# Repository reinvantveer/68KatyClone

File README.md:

# 68KatyClone
An open-hardware design for an 8-bit Motorola 68008 system.
Please feel free to re-use any of the parts enclosed in this repository, or see the [license](./LICENSE) for the hardware if in doubt.
However, the [monitor](Software/ROM/monitor.asm) and [Linux image](https://www.bigmessowires.com/68katy-files/uClinux-20040218.tar.gz) are both GNU GPL licensed, so these need care. Since I can't include the modified Linux image files in this repository itself (the file is too large to be included), I'll suffice by pointing you to [with a link](https://www.bigmessowires.com/68katy-files/uClinux-20040218.tar.gz). This was adapted from the [uCLinux original](https://web.archive.org/web/20181014184953/http://www.uclinux.org/pub/uClinux/dist/uClinux-dist-20040218.tar.gz). Ironically, the compiled binary image is small enough to fit into the 512k ROM, of course. 

**NOTE** This is a work in progress, by a guy with no prior experience in CPU board prototyping. Although I'm enjoying myself thoroughly and things are progressing well, this project comes without guarantees. 
* Update 17-03-202: I got my first address and data bus readouts today, using an Arduino Mega. It's not making much sense to me yet, but it soon will. It's clear that the processor is executing instructions!
* Update 15-03-2020: There is a working ['single-stepping' and power-up/reset schematic](KiCad/single-stepping.sch) that will serve as the basis for the rest of the project. The rest may or may not work, I'm not done debugging yet. 
* Update 22-03-2020: Made a few huge steps forward in having a working board, but I can't get a decent serial readout yet.  

# Credits
* This repository is my attempt to build a re-vamped edition of Steve "Big Mess-O-Wires" Chamberlin's [68Katy](https://www.bigmessowires.com/68-katy/), for which I owe him many thanks. It's my first go at breadboard prototyping, but since I'm learning so much I thought I'd contribute by publishing my findings. It has been quite the ride thus far. 
* Also, I'd like to point to Ben Eater's [6502 project](https://eater.net/6502), which has been quite inspirational. 
* I got myself a scope based on YouTubers [Adrians Digital Basement](https://www.youtube.com/channel/UCE5dIscvDxrb7CD5uiJJOiw) and [EEVblog](https://www.youtube.com/channel/UC2DjFE7Xf11URZqWBigcVOQ). 
* The [vid by John Tsiombikas](https://www.youtube.com/watch?v=rYkr1mFQ_50) helped me out hugely in putting together the single-stepping part of the board.  
* The power-up/reset circuit was based on a design [published by Jeff Tranter](https://github.com/jefftranter/68000/blob/master/TS2/v2.1/page1.sch)

I'm using the [68Katy](https://www.bigmessowires.com/68-katy/) design because it's pretty well documented, as Motorola 68K projects go. There's a lot of people experimenting, I even believe there's some kind of revival going of people baking 8-bit systems just for fun. The fact that a lot of the components can be ordered over the mail very cheaply most certainly adds to the fun - parts are available in abundance and even the shipping is often very cheap if you're willing to wait a couple of weeks. My guess is that these kinds of projects are being undertaken by late-30's to mid-50's guys tinkering away in sheds and attics. I happen to be just one of them. 

The reason I wanted to do a 68K project, is because I used to be, and still am, the proud owner of a Texas Instruments TI-92 that I bought in high school. At the time, I thought of it as a marvel of technology. I dabbled unsuccessfully in some C++ coding (I found it too hard), but the TI-92 allowed on-board BASIC programming an fancy graph plotting. So there my journey began. Now, over 20 years later, I'm a professional software developer and I believe I'm now better equipped for taking on the challenge of building an 8-bit system from bare components.

# Schematics
The [KiCad](KiCad) folder contains a work-in-progress translation of the schematics from Steve Chamberlin, updating it to a more modern version. I'm working on a board but at the moment it's not working. So use at your own peril.

# Memory Map

BREADBOARD 68 KATY
00000 - 77FFF : ROM
78000 - 79FFF : serial in        
7A000 - 7BFFF : serial out       
7C000 - 7DFFF : serial status    
7E000 - 7FFFF : LED register     
80000 - FFFFF : RAM              

# Software
## ROM image
The [ROM](Software/ROM) folder contains the ROM image: the monitor program and the Linux image. Send it to the ROM using a ROM programmer, I used a [TL866II plus](https://www.aliexpress.com/item/32963724045.html)

## GAL image
The [GAL/68katy](Software/GAL/68katy) folder contains the .jed compiled image. Send it to the GAL using a GAL-compatible ROM programmer, I used a [TL866II plus](https://www.aliexpress.com/item/32963724045.html)
For good measure I also included the [OpalJR compiler](Software/GAL/opaljr21) - as the license seems to allow it; I got it from [here](http://www.brouhaha.com/~eric/retrocomputing/mmi/palasm/opaljr21.zip). There's no reason not to include it here - it's the same program the original 68Katy GAL used to compile so it *should* be OK, although I can never be 100% sure unless I compare the JEDEC compiled file to the original (which I can't). Since it's a 16-bit DOS program, you need something like [DOSBox](https://www.dosbox.com/download.php?main=1) to run it.

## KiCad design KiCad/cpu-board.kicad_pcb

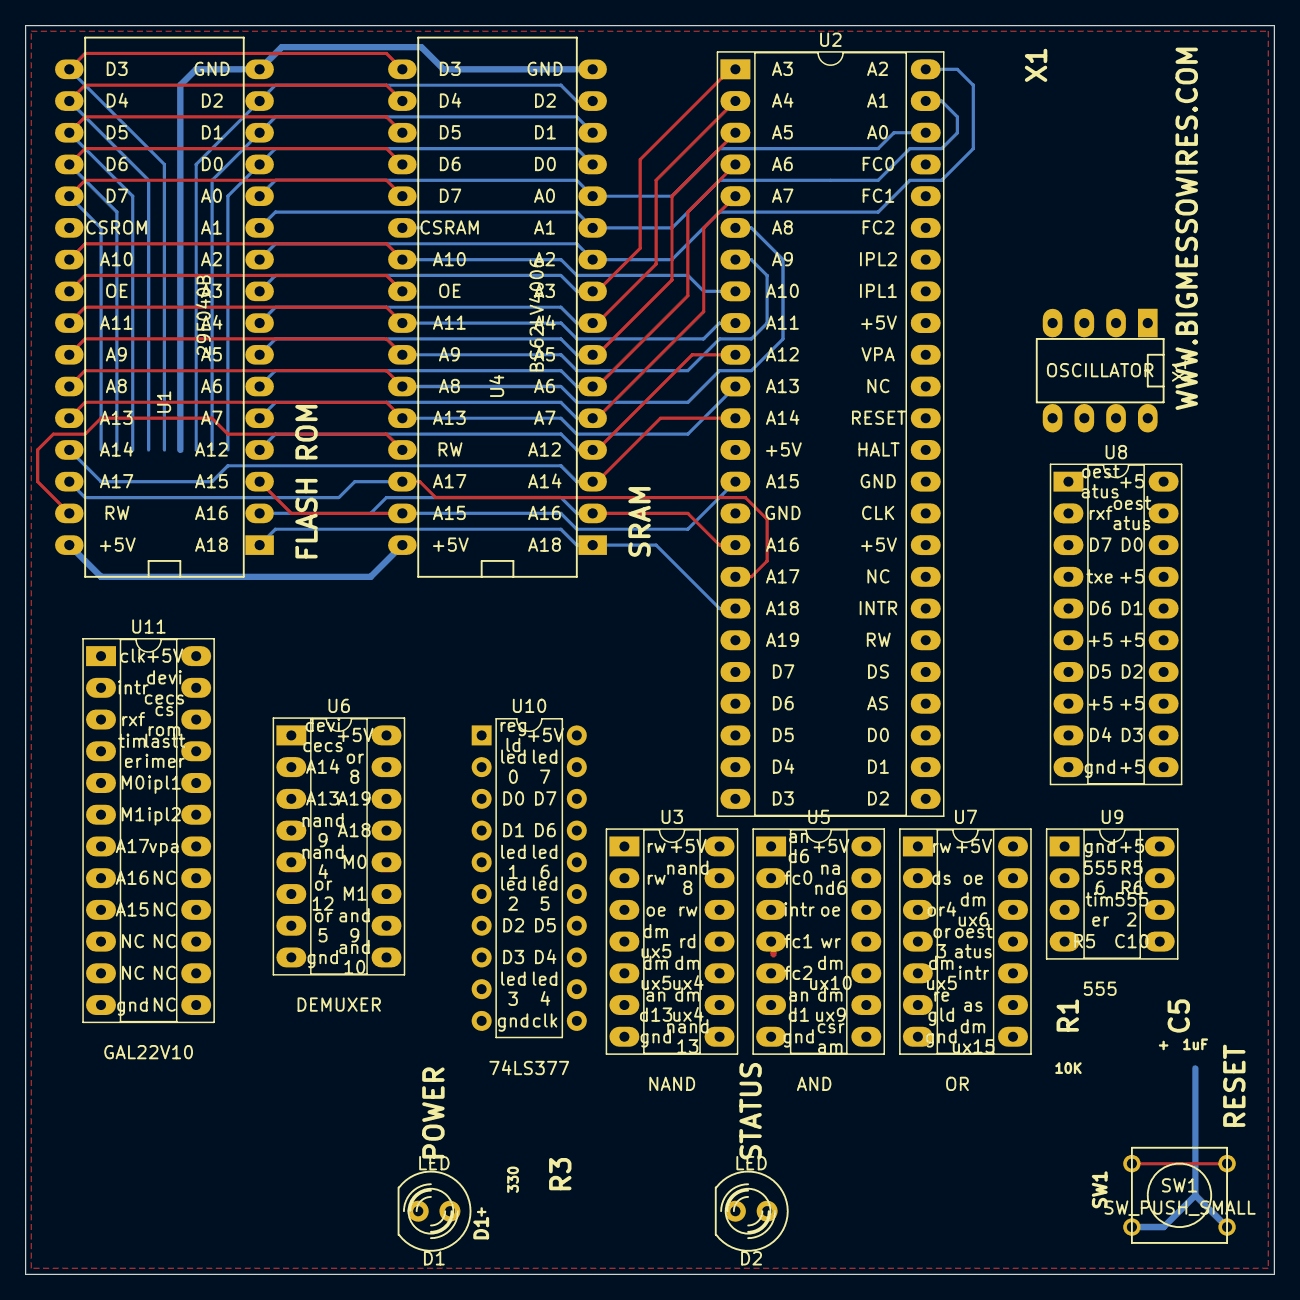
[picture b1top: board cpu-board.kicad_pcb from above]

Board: 2 copper layers, 100.0 x 100.0 mm, 15 parts (0 on the bottom side), 64 nets.

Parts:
D1, D2: LED; LED-5MM
SW1: SW_PUSH_SMALL
U1: 29F040B; DIP-32__600_ELL
U2: 68008D; DIP-48_W15.24mm_Socket_LongPads
U3: 74LS00; DIP-14_W7.62mm_Socket_LongPads
U4: BS62LV4006; DIP-32__600_ELL
U5: 74LS08; DIP-14_W7.62mm_Socket_LongPads
U6: 74LS139; DIP-16_W7.62mm_Socket_LongPads
U7: 74LS32; DIP-14_W7.62mm_Socket_LongPads
U8: 74LS244; DIP-20_W7.62mm_Socket_LongPads
U9: LM555; DIP-8_W7.62mm_Socket_LongPads
U10: 74LS377
U11: GAL22V10
X1: OSCILLATOR; DIP-8__300_ELL

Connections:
+5V: U1.32, U2.13, U2.33, U2.40, U4.32, U6.16, U8.6, U8.8, U8.11, U8.13, U8.15, U8.17, U8.20, U9.8, U10.20, U11.24, X1.8
/A0: U1.12, U2.46, U4.12
/A1: U1.11, U2.47, U4.11
/A2: U1.10, U2.48, U4.10
/A3: U1.9, U2.1, U4.9
/A4: U1.8, U2.2, U4.8
/A5: U1.7, U2.3, U4.7
/A6: U1.6, U2.4, U4.6
/A7: U1.5, U2.5, U4.5
/A8: U1.27, U2.6, U4.27
/A9: U1.26, U2.7, U4.26
/A10: U1.23, U2.8, U4.23
/A11: U1.25, U2.9, U4.25
/A12: U1.4, U2.10, U4.4
/A13: U1.28, U2.11, U4.28, U6.3
/A14: U1.29, U2.12, U4.3, U6.2
/A15: U1.3, U2.14, U4.31, U11.9
/A16: U1.2, U2.16, U4.2, U11.8
/A17: U1.30, U2.17, U4.30, U11.7
/A18: U1.1, U2.18, U4.1, U6.13
/A19: U2.19, U6.14
/AS: U2.28, U7.9
/CLK: U2.34, U10.11, U11.1, X1.5
/CSRAM: U4.22, U5.8
/CSROM: U1.22, U11.22
/D0: U1.13, U2.27, U4.13, U8.18, U10.3
/D1: U1.14, U2.26, U4.14, U8.16, U10.4
/D2: U1.15, U2.25, U4.15, U8.14, U10.7
/D3: U1.17, U2.24, U4.17, U8.12, U10.8
/D4: U1.18, U2.23, U4.18, U8.9, U10.13
/D5: U1.19, U2.22, U4.19, U8.7, U10.14
/D6: U1.20, U2.21, U4.20, U8.5, U10.17
/D7: U1.21, U2.20, U4.21, U8.3, U10.18
/DEVICECS: U6.1, U11.23
/DS: U2.29, U7.2
/FC0: U2.45, U5.2
/FC1: U2.44, U5.4
/FC2: U2.43, U5.5
/INTR: U2.31, U5.3, U7.10, U11.2
/IPL1: U2.41, U11.20
/IPL2: U2.42, U11.19
/M0: U6.12, U11.5
/M1: U6.11, U11.6
/OE: U1.24, U3.3, U4.24, U5.12, U7.13
/OESTATUS: U7.11, U8.1, U8.19
/REGLD: U7.6, U10.1
/RESET: SW1.1, U2.37
/RW: U1.31, U2.30, U3.1, U3.2, U3.12, U4.29, U7.1
/RXF: U8.2, U11.3
/TIMER: U9.3, U11.4
/VPA: U2.39, U11.18
GND: D1.2, SW1.2, U1.16, U2.15, U2.35, U4.16, U6.8, U8.10, U9.1, U10.10, U11.12, X1.4
unnamed: U9.2, U9.6
unnamed: U3.4, U3.5, U6.5
unnamed: U3.6, U5.13
unnamed: U3.9, U3.10, U6.4
unnamed: U3.8, U3.13
unnamed: U5.1, U5.6
unnamed: U5.9, U6.9
unnamed: U5.10, U6.10
unnamed: U6.6, U7.12
unnamed: U6.7, U7.5
unnamed: U6.15, U7.8
unnamed: U7.3, U7.4

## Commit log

2020-01-26 Rationale
2020-02-01 Include first rough version of KiCad schematics
2020-02-01 add gitignore
2020-02-01 add all in .idea dir
2020-02-01 Fix pin duplicates in schema for FIFO read/write logic
2020-02-01 add missing annotations
2020-02-01 add ROM image
2020-02-01 add missing annotation
2020-02-01 add GAL source and compiled JED file
2020-02-01 add Opal Jr. binaries
2020-02-01 include dosbox instruction
2020-02-01 add Opal Jr provenance
2020-02-05 add footprints to schema, add chips to board layout
2020-02-05 add missing pull-up resistors for TXE and RXF
2020-02-05 annotate pull-up resistors
2020-02-05 connect pull-ups to +5V
2020-02-06 associate 20-pin TTL 377 and 244 with long-pad socket footprints
2020-02-06 switch demuxer footprint for long-pad socket, clean up old traces
2020-02-08 fix errors in PCB pin labels
2020-02-08 add some address lines for fun
2020-02-08 re-order imagery and components for clarity, add wire from C8 to FT245 breakout board VCCIO
2020-02-09 add some address bus tracks
2020-02-29 fix schema error on disconnecte Vcc to pin 4 on 555 timer
2020-03-03 single-stepping schema from John Tsiombikas
2020-03-03 commit vscode settings
2020-03-03 get the FT245 project file in there
2020-03-03 using the long pads sockets for DIP16 and DIP20
2020-03-04 add single-stepped CPU symbol to schema, with LED to blink
2020-03-12 fix halt and error line high to pulled high, add power-up reset circuitry
2020-03-15 Add reset switch
2020-03-15 Add/refactor credits section
2020-03-15 Small re-ordering of components in power-up section
2020-03-17 re-order pin configuration, trigger on DTACK
2020-03-20 First working version of sketch. Pins in reverse order, looks like
2020-03-20 Include source of monitor assembly file
2020-03-20 fix reverse pin order, add address mapping
2020-03-20 Document some sources
2020-03-20 Pretty-print binary and hex into fixed-width table
2020-03-20 whitespace, comments
2020-03-21 re-label active-low pins with bars
2020-03-22 Declare arduino type, higher baudrate to catch things happening
2020-03-22 add original Linux source link, add update
2020-04-05 remove data bus LEDs, they are of little use
2020-04-05 disconnect unused data strobe line
2020-04-20 Create Firmata controller with a few basic methods of operating the m68k
2020-04-20 first test functions for checking basic operation: cycling through part of the address space
2020-04-27 use test harness from Arduino C++, it's much faster
2020-04-28 move development to platformio
2020-04-29 Add comments top section
2020-05-02 fix freerun test, run serial at 115k baud
2020-05-03 extract more hardware functions to header, increase dtack_pulse to 10 ms each
2020-05-03 add include dir
2020-05-03 add address bus read to loop to measure performance
2020-05-03 add previously ignored arduino libraries
2020-05-03 simplify address check/logging
2020-05-03 improve test output as single line with percentage complete
2020-05-03 Improve messaging, some refactoring
2020-05-04 move functional tests to aptly named folder
2020-05-04 move test
2020-05-04 move main code to main.cpp
2020-05-08 add selection menu
2020-05-08 add ROM test scaffold
2020-05-08 remove dtack and address check from loop to fix freerun error
2020-05-08 cosmetics
2020-05-08 correct description of first 8 data cycles
2020-05-09 Add memory map
2020-05-09 refactor: extract out address bus operation
2020-05-09 fix indentation
2020-05-09 safe include hardware control functions
2020-05-09 whitespace
2020-05-09 make rom hash function, set pins, reset
2020-05-09 use define to set import flag
2020-05-09 move address and data bus specifics to header
2020-05-09 extract out data bus operation, cleanup
2020-05-09 clean up
2020-05-10 extract stack pointer and program counter as separate function and include in reset_setup
2020-05-13 refactor: add function for printing out the data bus pin mapping
2020-05-13 refactor: add address bus mapping print function
2020-05-13 WIP add more debugging to rom test
2020-05-13 cleanup
2020-05-13 Move prep and print steps to setup
2020-05-19 fix boot code operation, faster reset_setup
2020-05-19 add menu options for basic operations
2020-05-22 Work in progress: fiddle around with hex op-codes
2020-05-22 prettier printing, add data strobe input
2020-05-22 humble beginnings of a struct-based interface board object
2020-05-22 instantiate interface board object, attach interrupt to data strobe, prettier printing
2020-05-22 Move serial comms and baudrate to Mega2M68k8 struct
2020-05-24 Remove unused struct
2020-05-24 Move basic setup and config back to main
2020-05-24 Clean up, improve logging
2020-05-24 Don't log every pin mapping
2020-05-24 refactor: log data bytes as hex representation of unsigned chars
2020-06-07 improve documentation and logging
